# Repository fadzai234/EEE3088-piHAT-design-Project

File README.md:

# EEE3088-piHAT-design-Project
The objective of this project is to design a raspberry piHAT which can sense and log temperatures in environments such as refrigerators and geysers.

The piHAT will be attached to the raspberry pi zero which wil be used to record the temperature measurements which are recieved from a pre-designed temperature sensor board.

The sense microHat will sense and monitor temperature readings. The Hat will be attached to a predesigned sensor that will measure the temperature as a function of voltage and this will be converted to degrees using an analogue to digital convertor. This microHat can be used in a home weather station to measure environmental temperature, in electronic devices or in home automation systems such as a geyser.

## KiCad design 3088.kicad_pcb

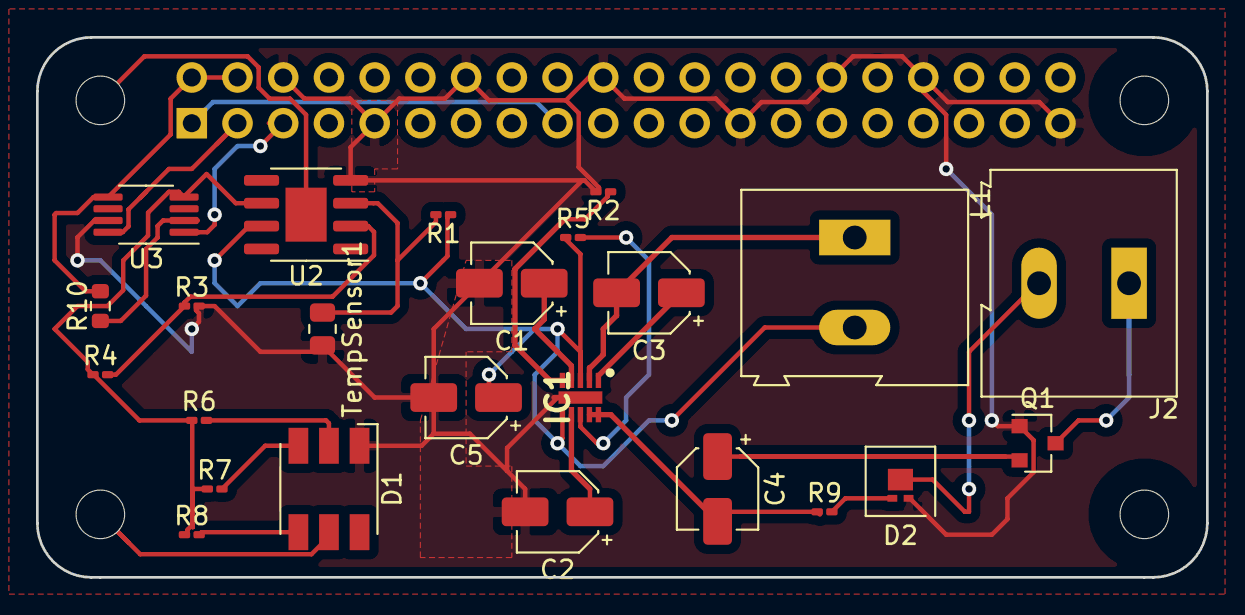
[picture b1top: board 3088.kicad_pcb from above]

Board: 2 copper layers, 65.0 x 30.0 mm, 29 parts (1 on the bottom side), 23 nets.

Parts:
C1: 1u; CP_Elec_4x3
C2, C5: 10n; CP_Elec_4x3
C3: 0.047u; CP_Elec_4x3
C4: 2.2u; CP_Elec_4x3
D1: LED_ABGR; LED_RGB_5050-6
D2: LED; LED-L1T2_LUMILEDS
H1, H2, H3, H4: MountingHole; MountingHole_2.7mm_M2.5_uHAT_RPi
IC1: LT8618EDDB-3.3#TRPBF; SON50P200X300X80-11N-D
J1: GPIO_CONNECTOR; PinSocket_2x20_P2.54mm_Vertical_Centered_Anchor
J2: Screw_Terminal_01x01; TerminalBlock_Altech_AK300-2_P5.00mm
L1: 120u; TerminalBlock_Altech_AK300-2_P5.00mm
Q1: AO3401A; SOT-23
R1: 4700; R_0201_0603Metric_Pad0.64x0.40mm_HandSolder
R2: 110k; R_0201_0603Metric_Pad0.64x0.40mm_HandSolder
R3: 5000; R_0201_0603Metric_Pad0.64x0.40mm_HandSolder
R4: 47000; R_0201_0603Metric_Pad0.64x0.40mm_HandSolder
R5: 100k; R_0201_0603Metric_Pad0.64x0.40mm_HandSolder
R6: 47.5; R_0201_0603Metric_Pad0.64x0.40mm_HandSolder
R7: 40; R_0201_0603Metric_Pad0.64x0.40mm_HandSolder
R8: 12.5; R_0201_0603Metric_Pad0.64x0.40mm_HandSolder
R9: 100; R_0201_0603Metric_Pad0.64x0.40mm_HandSolder
R10: 5000; R_0603_1608Metric
TempSensor1: PT100; R_0805_2012Metric
U2: LM741; SOIC-8-1EP_3.9x4.9mm_P1.27mm_EP2.29x3mm
U3: ADC081C021CIMM; MSOP-8_3x3mm_P0.65mm

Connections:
+3V3: J1.1, J1.17
+5V: J1.2, J1.4, R10.2, U3.5
+12V: J2.1, Q1.3
GND: C1.2, C2.2, C5.2, D1.1, D2.1, IC1.11, J1.6, J1.9, J1.14, J1.20, J1.25, J1.30, J1.34, J1.39, Q1.1, R2.2, R3.2, TempSensor1.2, U2.4, U3.7
unnamed: C4.1, Q1.2
unnamed: D1.2, R6.2
unnamed: D1.3, R7.2
unnamed: D1.4, R8.2
unnamed: D2.2, R9.2
unnamed: R1.2, TempSensor1.1, U2.3
unnamed: R3.1, R4.2, U2.2
unnamed: R10.1, U3.2
OUT: C5.1, IC1.3, IC1.6, L1.2, R1.1, R5.1, U2.7
SCL: J1.5, U3.1
SDA: J1.3, U3.8
VopAmpOut: R4.1, R6.1, R7.1, R8.1, U2.6, U3.4
Vreg_BST: C3.1, IC1.1
Vreg_ENUV: C4.2, IC1.9, IC1.10, R9.1
Vreg_INTVCC: C1.1, IC1.4
Vreg_PG: IC1.8, R5.2
Vreg_RT: IC1.5, R2.1
Vreg_SW: C3.2, IC1.2, L1.1
Vreg_TRSS: C2.1, IC1.7

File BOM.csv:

"Source:","C:\Users\Fadzai\Desktop\Academic 2021\eee3088\Proj1\3088\3088.sch"
"Date:","2021/06/13 10:51:07"
"Tool:","Eeschema (5.1.10)-1"
"Generator:","C:\Program Files\KiCad\bin\scripting\plugins/bom_csv_grouped_by_value_with_fp.py"
"Component Count:","31"
"Ref","Qnty","Value","Cmp name","Footprint","Description","Vendor"
"C1, ","1","1u","C","Capacitor_SMD:CP_Elec_4x3","Capacitor symbol for simulation only",""
"C2, C5, ","2","10n","C","Capacitor_SMD:CP_Elec_4x3","Capacitor symbol for simulation only",""
"C3, ","1","0.047u","C","Capacitor_SMD:CP_Elec_4x3","Capacitor symbol for simulation only",""
"C4, ","1","2.2u","C","Capacitor_SMD:CP_Elec_4x3","Capacitor symbol for simulation only",""
"D1, ","1","LED_BCGR","LED_BCGR","LED_SMD:LED_0201_0603Metric","RGB LED, blue/cathode/green/red",""
"D2, ","1","LED","LED","LED_SMD:LED-L1T2_LUMILEDS","Light emitting diode",""
"H1, H2, H3, H4, ","4","MountingHole","MountingHole","lib:MountingHole_2.7mm_M2.5_uHAT_RPi","Mounting Hole without connection",""
"IC1, ","1","LT8618EDDB-3.3#TRPBF","LT8618EDDB-3.3#TRPBF","LT8618EDDB-3.3#TRPBF:SON50P200X300X80-11N-D","Switching Voltage Regulators High Efficiency 60V/100mA Synchronous Bu",""
"J1, ","1","GPIO_CONNECTOR","Conn_02x20_Odd_Even","lib:PinSocket_2x20_P2.54mm_Vertical_Centered_Anchor","Generic connector, double row, 02x20, odd/even pin numbering scheme (row 1 odd numbers, row 2 even numbers), script generated (kicad-library-utils/schlib/autogen/connector/)",""
"J2, ","1","Screw_Terminal_01x01","Screw_Terminal_01x01","TerminalBlock:TerminalBlock_Altech_AK300-2_P5.00mm","Generic screw terminal, single row, 01x01, script generated (kicad-library-utils/schlib/autogen/connector/)",""
"L1, ","1","120u","INDUCTOR","TerminalBlock:TerminalBlock_Altech_AK300-2_P5.00mm","Inductor symbol for simulation only",""
"Q1, ","1","AO3401A","AO3401A","Package_TO_SOT_SMD:SOT-23","-4.0A Id, -30V Vds, P-Channel MOSFET, SOT-23",""
"Q2, ","1","2N2219","2N2219","Package_TO_SOT_THT:TO-39-3","800mA Ic, 50V Vce, NPN Transistor, TO-39",""
"R1, ","1","4700","R","Resistor_SMD:R_0201_0603Metric_Pad0.64x0.40mm_HandSolder","Resistor",""
"R2, ","1","110k","R_Small","Resistor_SMD:R_0201_0603Metric_Pad0.64x0.40mm_HandSolder","Resistor, small symbol",""
"R3, ","1","5000","R","Resistor_SMD:R_0201_0603Metric_Pad0.64x0.40mm_HandSolder","Resistor",""
"R4, ","1","47000","R","Resistor_SMD:R_0201_0603Metric_Pad0.64x0.40mm_HandSolder","Resistor",""
"R5, ","1","100k","R_Small","Resistor_SMD:R_0201_0603Metric_Pad0.64x0.40mm_HandSolder","Resistor, small symbol",""
"R6, ","1","47.5","R","Resistor_SMD:R_0201_0603Metric_Pad0.64x0.40mm_HandSolder","Resistor",""
"R7, ","1","40","R","Resistor_SMD:R_0201_0603Metric_Pad0.64x0.40mm_HandSolder","Resistor",""
"R8, ","1","12.5","R","Resistor_SMD:R_0201_0603Metric_Pad0.64x0.40mm_HandSolder","Resistor",""
"R9, ","1","330","R_Small","Resistor_SMD:R_0201_0603Metric_Pad0.64x0.40mm_HandSolder","Resistor, small symbol",""
"R10, ","1","5000","R_Small","Resistor_SMD:R_0603_1608Metric","Resistor, small symbol",""
"TempSensor1, ","1","PT100","PT100","Resistor_SMD:R_0805_2012Metric","PT100 platinum temperature sensor (RTD)",""
"U2, ","1","LM741","LM741","Package_SO:SOIC-8-1EP_3.9x4.9mm_P1.27mm_EP2.29x3mm","Operational Amplifier, DIP-8/TO-99-8",""
"U3, ","1","ADC081C021CIMM","ADC081C021CIMM","Package_SO:MSOP-8_3x3mm_P0.65mm","I2C-Compatible, 8-Bit Analog-to-Digital Converter with Alert Function, MSOP-8",""
"ZVD1, ","1","DIODE","DIODE","Diode_SMD:D_0201_0603Metric","Diode symbol for simulation only. Pin order incompatible with official kicad footprints",""

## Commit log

2021-05-13 Create LICENSE
2021-05-31 Add files via upload
    Added uHat template.
2021-05-31 Add files via upload
    status led schematics
2021-06-01 Add files via upload
    lt spice files for op amp circuit
2021-06-02 Add files via upload
    new led schematic
2021-06-02 Added micro-piHAT v1.0
2021-06-03 The ERC report to show no errors
2021-06-03 The generated netlist file
2021-06-03 deleting old status led files
2021-06-03 adding lt spice
2021-06-03 new folder containing all files
2021-06-04 Added Voltage regulator schematic from kicad
2021-06-04 Added the project kicad files for version 2
2021-06-04 adding the op amp circuit kicad schematics
2021-06-04 final pcb files for the pi hat project
2021-06-04 Added the LT8618 part for KICAD
    The symbol and footprints are included.
2021-06-05 Added LtSpice schematics for the Voltage reg
2021-06-11 deletin old led file
2021-06-11 adding led kiCAD schemtic
2021-06-11 uploadin new ltspice schematic in LTSpice
2021-06-11 how the LEDs work
2021-06-13 Added the LTSpice schematic for the voltage regulator
    THe input voltage is 12V and the output is 3.3V
2021-06-13 The LTspice simulation for the output voltage of the Voltage regulator
    The file "Vout for Vreg.png" shows the output voltage when the nominal input voltage of 12V is applied. The file "V_reg for range of input Voltages.png" shows the output voltage when the range of inp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
2021-06-13 Lt Spice simulations for the output current of the Voltage regulator
    The output current was simulated for a range of voltages from 11.5V to 12.5V. The outout current satisfies the requirement for output current of the PT100 to be between 0.1mA to 1mA since it settles 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
2021-06-13 Output current simulation for Voltage regulator output
    The PSU satisfies the maximum output current specification which is that the max output current must be<1mA. For the range of PT100 resistor values used the maximum current will be 0.6mA.
2021-06-13 Added power supply module Version 2 KICAD schematic
2021-06-13 Document detailing the requirements and specifications of piHAT
2021-06-13 Bill of Materials
2021-06-13 KICAD schematic of op-amp sub-module
2021-06-14 Create Getting started
2021-06-14 Op Amp Simulations
2021-06-14 Create How the LEDs work
2021-06-18 Manufacturing Notes
2021-06-18 Added DRC report
    The DRC reported no unconnected components, however, the other errors were due to e.g pads being too close to pads which was due to the inherent nature of the components used.
2021-06-18 Added PCB v2
    This version of the pcb hs 2 layers instead of 4 which is more approprate for this system.
2021-06-18 Added the other files necessary forthe pcb

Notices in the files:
3088.kicad_pcb:
This PCB design is licensed under MIT Open Source License.
